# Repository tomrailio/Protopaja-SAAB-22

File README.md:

# Protocamp-22 / SAAB handheld microwave transmitter.
Protopaja (Protocamp) is a 10 ECTS summerproject course in the University of Aalto to create 
functional interactive prototypes based on briefs by partnering companies. 
The School of Electrical Engineering is the organizational unit and the 
Teachers in charge: Salu Ylirisku and Kimmo Silvonen (kimmo.silvonen@aalto.fi)

SAAB recently developed the passive 'Sirius Compact' radar system for warfare. Now SAAB wants 
to develop a tool to test the limits and potential of the system. The Sirius Compact sensor 
network has been developed specifically with Electronic Warfare (EW) in mind. Modular as 
well as scalable, Sirius Compact's primary use case is seen as providing tactical-level 
situational awareness for warfare from battlefields by generating electromagnetic activity 
imaging with its sensors that detect electromagnetic radiation. In addition to this, Sirius 
Compact is also capable of predicting, classifying and prioritising radar and data link 
signals in the environment. SAAB needs a test tool for the radar system. The purpose of 
this project work is to create the desired test tool. 

The software will be published under a very permissive MIT license. See the licence file 
disclosed in this repository for further details.

# Schematics, PCB blueprint as well as part lists are located in Schematics folder

Technical Specifications:

  * Power level < 20 dBm EIRP (antenna gain + output power).

  * Frequency is 2.4 GHz.

  * Waveform: Continuous wave (narrow bandwidth).

  * Transmitter will be targeted manually by pointing.

Non-functional requirements:

  * Usability.

  * Reliability.

  * Performance.

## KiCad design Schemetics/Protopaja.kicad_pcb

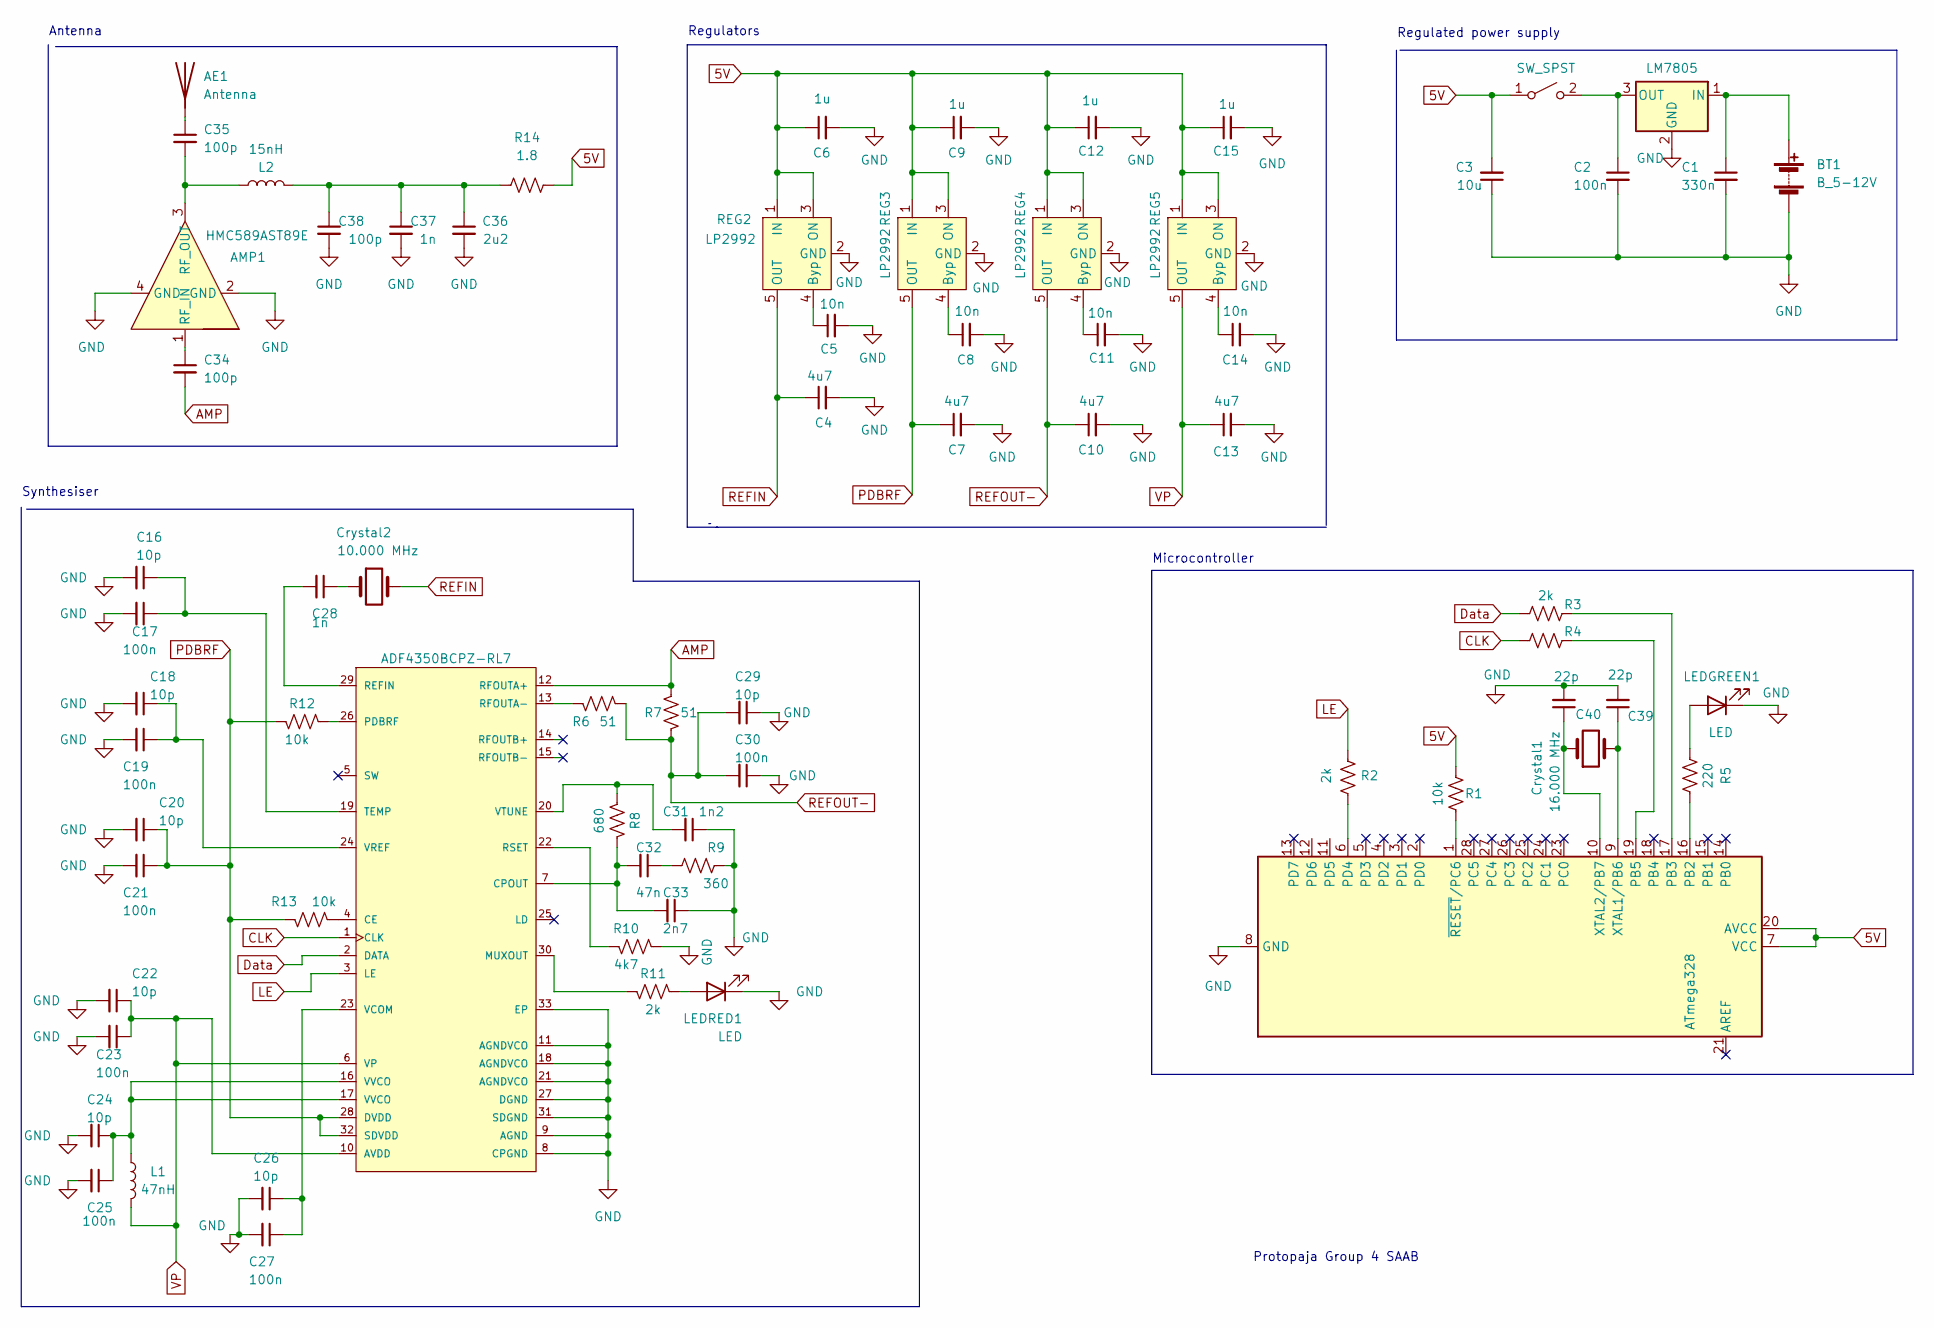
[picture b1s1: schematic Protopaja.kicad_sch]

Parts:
ADF4350BCPZ-RL7: ADF4350BCPZ-RL7; LFCSP-32-1EP_5x5mm_P0.5mm_EP3.25x3.25mm
AE1: Antenna; U.FL_Molex_MCRF_73412-0110_Vertical
AMP1: HMC589AST89E; HMC
ATmega328: ATmega328-P; DIP-28_W7.62mm
BT1: B_5-12V; AMASS_XT60-F_1x02_P7.20mm_Vertical
C1: 330n; C_0603_1608Metric
C2, C17, C19, C21, C23, C25, C27, C30: 100n; C_0603_1608Metric
C3: 10u; C_0805_2012Metric
C4, C7, C10, C13: 4u7; C_0805_2012Metric
C5, C8, C11, C14: 10n; C_0603_1608Metric
C6, C9, C12, C15: 1u; C_0603_1608Metric
C16, C18, C20, C22, C24, C26, C29: 10p; C_0603_1608Metric
C28: 1n; C_0603_1608Metric
C31: 1n2; C_0603_1608Metric
C32: 47n; C_0603_1608Metric
C33: 2n7; C_0201_0603Metric
C34, C35: 100p; C_0603_1608Metric
C36: 2u2; C_0805_2012Metric
C37: 1n; C_0805_2012Metric
C38: 100p; C_0805_2012Metric
C39, C40: 22p; C_0603_1608Metric
Crystal1: 16.000 MHz; Crystal_HC18-U_Vertical
Crystal2: 10.000 MHz; CFPS
L1: 47nH; L_0402_1005Metric
L2: 15nH; L_0402_1005Metric
LEDGREEN1: LED; LED_D2.0mm_W4.8mm_H2.5mm_FlatTop
LEDRED1: LED; LED_D2.0mm_W4.8mm_H2.5mm_FlatTop
LM7805: L7805; SolderWire-0.5sqmm_1x03_P4.8mm_D0.9mm_OD2.3mm
R1, R12, R13: 10k; R_0603_1608Metric_Pad0.98x0.95mm_HandSolder
R2, R3, R4, R11: 2k; R_0603_1608Metric_Pad0.98x0.95mm_HandSolder
R5: 220; R_0603_1608Metric_Pad0.98x0.95mm_HandSolder
R6, R7: 51; R_0603_1608Metric_Pad0.98x0.95mm_HandSolder
R8: 680; R_0603_1608Metric_Pad0.98x0.95mm_HandSolder
R9: 360; R_0603_1608Metric_Pad0.98x0.95mm_HandSolder
R10: 4k7; R_0603_1608Metric_Pad0.98x0.95mm_HandSolder
R14: 1.8; R_0603_1608Metric
REG2, REG3, REG4, REG5: LP2992
SW2: SW_SPST; SolderWire-0.5sqmm_1x02_P4.6mm_D0.9mm_OD2.1mm

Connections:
5V: ATmega328.7 (VCC), ATmega328.20 (AVCC), C3.2, C6.1, C9.1, C12.1, C15.1, R1.2, R14.2, REG2.1 (IN), REG2.3 (ON), REG3.1 (IN), REG3.3 (ON), REG4.1 (IN), REG4.3 (ON), REG5.1 (IN), REG5.3 (ON), SW2.1 (A)
AMP: ADF4350BCPZ-RL7.12 (RFOUTA+), C34.2, R7.2
CLK: ADF4350BCPZ-RL7.1 (CLK), R4.1
Data: ADF4350BCPZ-RL7.2 (DATA), R3.1
LE: ADF4350BCPZ-RL7.3 (LE), R2.1
unnamed: ADF4350BCPZ-RL7.4 (CE), R13.2
unnamed: ADF4350BCPZ-RL7.7 (CPOUT), C32.2, C33.2, R8.1
unnamed: ADF4350BCPZ-RL7.13 (RFOUTA-), R6.1
unnamed: ADF4350BCPZ-RL7.16 (VVCO), ADF4350BCPZ-RL7.17 (VVCO), C24.1, C25.1, L1.1
unnamed: ADF4350BCPZ-RL7.19 (TEMP), C16.1, C17.1
unnamed: ADF4350BCPZ-RL7.20 (VTUNE), C31.2, R8.2
unnamed: ADF4350BCPZ-RL7.22 (RSET), R10.1
unnamed: ADF4350BCPZ-RL7.23 (VCOM), C26.1, C27.1
unnamed: ADF4350BCPZ-RL7.24 (VREF), C18.1, C19.1
unnamed: ADF4350BCPZ-RL7.26 (PDBRF), R12.2
unnamed: ADF4350BCPZ-RL7.29 (REFIN), C28.2
unnamed: ADF4350BCPZ-RL7.30 (MUXOUT), R11.1
unnamed: AE1.1 (A), C35.1
unnamed: AMP1.1 (RF_IN), C34.1
unnamed: AMP1.3 (RF_OUT), C35.2, L2.1
unnamed: ATmega328.1 (~RESET/PC6), R1.1
unnamed: ATmega328.6 (PD4), R2.2
unnamed: ATmega328.9 (XTAL1/PB6), C39.1, Crystal1.2
unnamed: ATmega328.10 (XTAL2/PB7), C40.1, Crystal1.1
unnamed: ATmega328.16 (PB2), R5.2
unnamed: ATmega328.17 (PB3), R3.2
unnamed: ATmega328.19 (PB5), R4.2
unnamed: BT1.1 (+), C1.1, LM7805.1 (IN)
unnamed: C2.1, LM7805.3 (OUT), SW2.2 (B)
unnamed: C5.1, REG2.4 (Byp)
unnamed: C8.1, REG3.4 (Byp)
unnamed: C11.1, REG4.4 (Byp)
unnamed: C14.1, REG5.4 (Byp)
unnamed: C32.1, R9.1
unnamed: C36.1, C37.1, C38.1, L2.2, R14.1
unnamed: LEDGREEN1.2 (A), R5.1
unnamed: LEDRED1.2 (A), R11.2
PDBRF: ADF4350BCPZ-RL7.28 (DVDD), ADF4350BCPZ-RL7.32 (SDVDD), C7.1, C20.1, C21.1, R12.1, R13.1, REG3.5 (OUT)
REFOUT-: C10.1, C29.2, C30.2, R6.2, R7.1, REG4.5 (OUT)
VP: ADF4350BCPZ-RL7.6 (VP), ADF4350BCPZ-RL7.10 (AVDD), C13.1, C22.1, C23.1, L1.2, REG5.5 (OUT)

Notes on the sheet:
Protopaja Group 4 SAAB
Antenna
Microcontroller
Regulators
Synthesiser
Regulated power supply

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
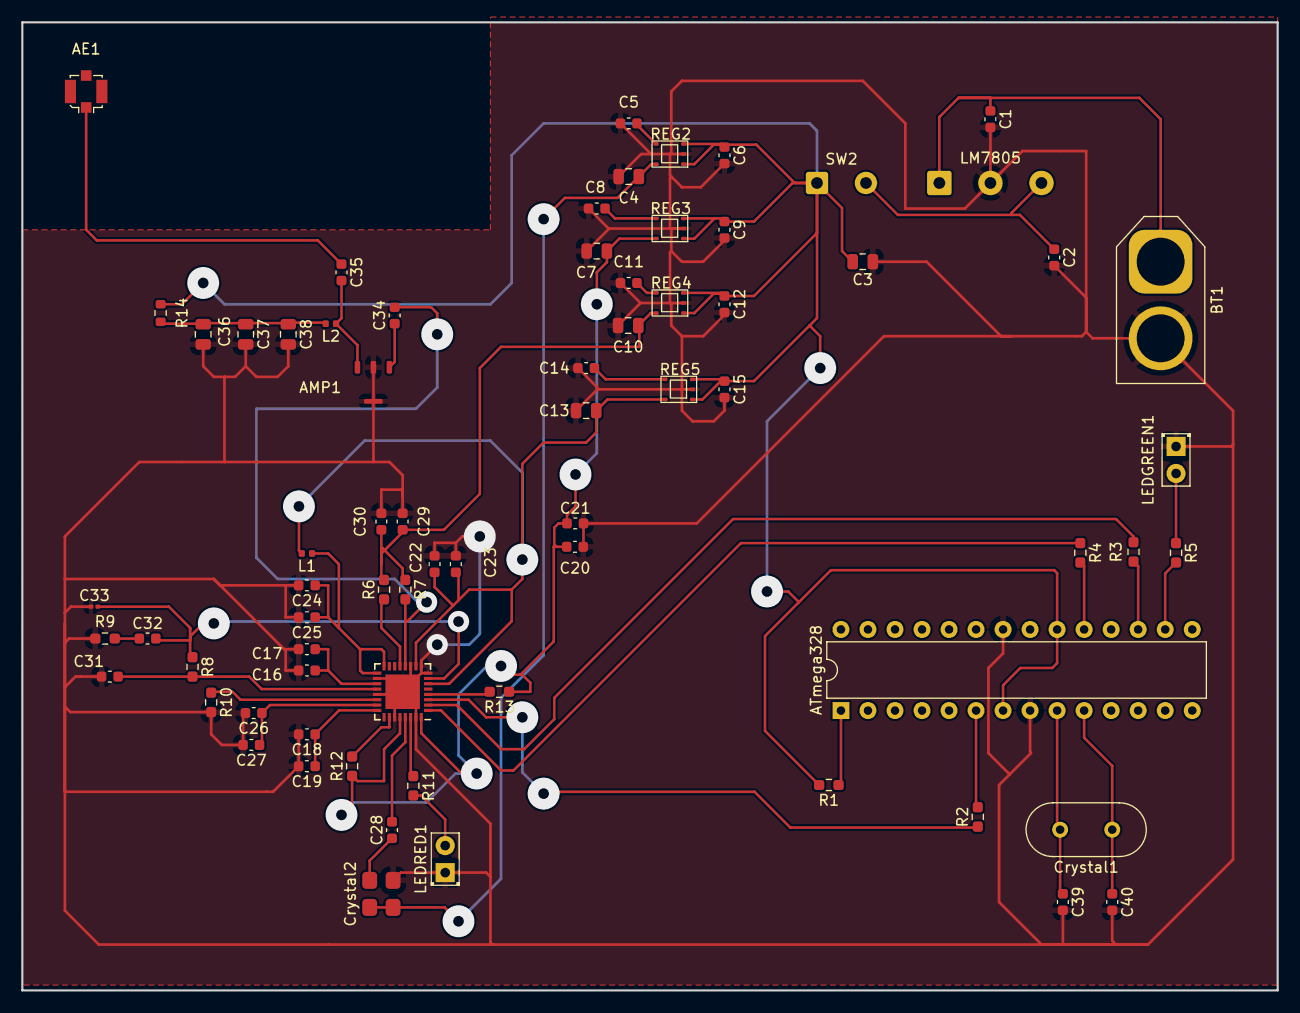
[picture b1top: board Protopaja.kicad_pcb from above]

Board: 2 copper layers, 118.0 x 91.0 mm, 71 parts (0 on the bottom side), 43 nets.

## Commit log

2022-06-12 Create Gantt for Saab 1st Sprints
2022-06-20 Create Versions 1.01++
2022-06-20 Create BLINK test Function.
2022-06-20 Update Versions 1.01++
2022-06-20 Update BLINK test Function.
2022-06-20 Timeline
2022-06-21 Create Death-Star-Code
2022-06-21 Create Library used: WiFi
2022-06-21 Create Detected Bugs & fixes.
2022-06-22 Create signalpressButton
2022-06-22 Rename signalpressButton to SIGNAL pressButton
2022-06-22 Update SIGNAL pressButton
2022-06-22 Create SIGNAL pressButton 1st Draft
2022-06-22 Update SIGNAL pressButton 1st Draft
2022-06-22 Create SIGNAL pressButton 2nd Draft
2022-06-22 Update SIGNAL pressButton 2nd Draft
2022-06-27 Create Signal measurement
2022-06-27 Create Library used: Button
2022-06-27 Update Signal measurement
2022-06-28 Create Wi-Fi & VNA test setting
2022-06-28 Update Wi-Fi & VNA test setting
2022-06-29 Create SIGNAL PressButton 3rd draft
2022-06-29 Update SIGNAL PressButton 3rd draft
2022-06-29 Update Death-Star-Code
2022-07-04 Create Datasheet
2022-07-04 Update Datasheet
2022-07-04 Update Detected Bugs & fixes.
2022-07-18 Create Signal PressButton 4rd draft
2022-07-18 Update Signal PressButton 4rd draft
2022-07-18 Added example code for the device, created directory for past code snippets and notes
2022-07-25 Create TODOs
2022-07-25 Update TODOs
2022-07-27 Create Death-Star-Code-2
2022-08-01 Create LICENCE
2022-08-01 Update LICENCE
2022-08-03 Create Component block diagramme
2022-08-03 Create Block Diagram
2022-08-10 Create Matlab snippets for measurement plots
2022-08-10 Update Matlab snippets for measurement plots
2022-08-11 Updated synthesizer registers values
2022-08-12 Create Prototype source code
2022-08-12 Update Prototype source code
2022-08-12 Create Snippets for additional diagrammes.
2022-08-12 Update Snippets for additional diagrammes.
2022-08-12 Create Detected problems and fixes.
2022-08-12 Update Detected problems and fixes.
2022-08-22 Added 3d models for the case
2022-08-22 changed arduino file name
2022-08-22 Deleted redundant files and folders
2022-08-23 Moved schematics to Schematics folder and added parts name and information in Schematics/Schematic details
2022-08-23 Added battery detail to Schematic details file
2022-08-29 Added additional instrucitoons in README file
